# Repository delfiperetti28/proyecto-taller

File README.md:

Proyecto dedicado a la fabricación de un pastillero automatico

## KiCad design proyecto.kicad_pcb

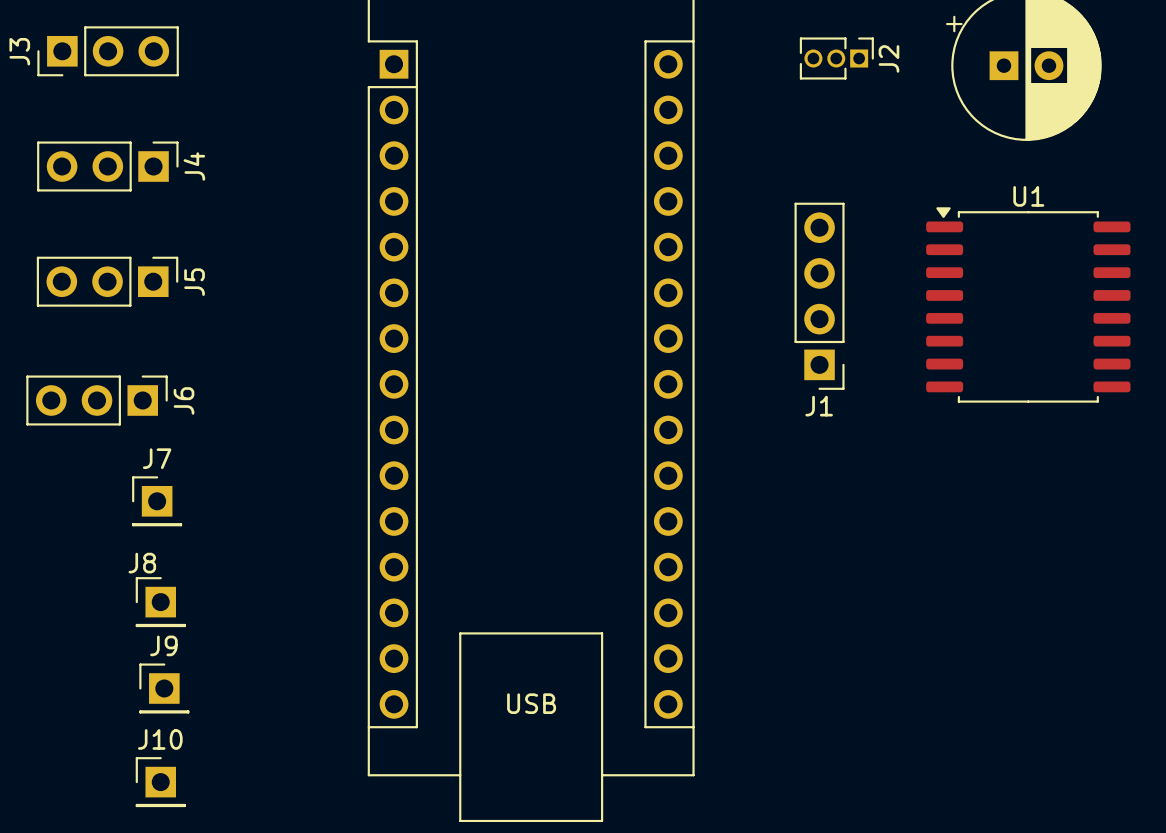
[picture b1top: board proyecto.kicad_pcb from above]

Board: 2 copper layers, 13 parts (0 on the bottom side), 14 nets, no tracks yet.

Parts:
A1: Arduino_Nano_Every; Arduino_Nano
C1: C; CP_Radial_D8.0mm_P2.50mm
J1: Conn_01x04_Pin; PinHeader_1x04_P2.54mm_Vertical
J2: Conn_01x03_Pin; PinHeader_1x03_P1.27mm_Vertical
J3, J4, J5, J6: Conn_01x03_Pin; PinHeader_1x03_P2.54mm_Vertical
J7, J8, J9, J10: Conn_01x02_Pin; PinHeader_1x01_P2.54mm_Vertical
U1: DS3231M; SOIC-16W_7.5x10.3mm_P1.27mm

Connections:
GND: A1.4 (GND), A1.29 (GND), C1.2, J1.1, J2.3, J3.3, J4.1, J4.3, J5.1, J5.3, J6.1, J6.3, U1.5 (GND), U1.6 (GND), U1.7 (GND), U1.8 (GND), U1.9 (GND), U1.10 (GND), U1.11 (GND), U1.12 (GND), U1.13 (GND)
unnamed: A1.27 (+5V), J1.4, U1.2 (VCC)
unnamed: A1.5 (D2), J2.2
unnamed: A1.6 (D3), J3.2
unnamed: A1.7 (D4), J4.2
unnamed: A1.8 (D5), J5.2
unnamed: A1.9 (D6), J6.2
unnamed: A1.10 (D7), J7.1
unnamed: A1.11 (D8), J8.1
unnamed: A1.12 (D9), J9.1
unnamed: A1.13 (D10), J10.1
unnamed: A1.24 (SCL/A5), J1.3, U1.16 (SCL)
unnamed: A1.23 (SDA/A4), J1.2, U1.15 (SDA)
VCC: A1.30 (VIN), C1.1, J2.1, J3.1
